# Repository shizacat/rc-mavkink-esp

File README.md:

# Description

This is hardware adapter for ESP8266 (ESP12E). The project made in Eagle.

Feature:

- Tolerant to 3.3 - 5V power supply

Firmware: [dogmaphobic/mavesp8266](https://github.com/dogmaphobic/mavesp8266)

Example:

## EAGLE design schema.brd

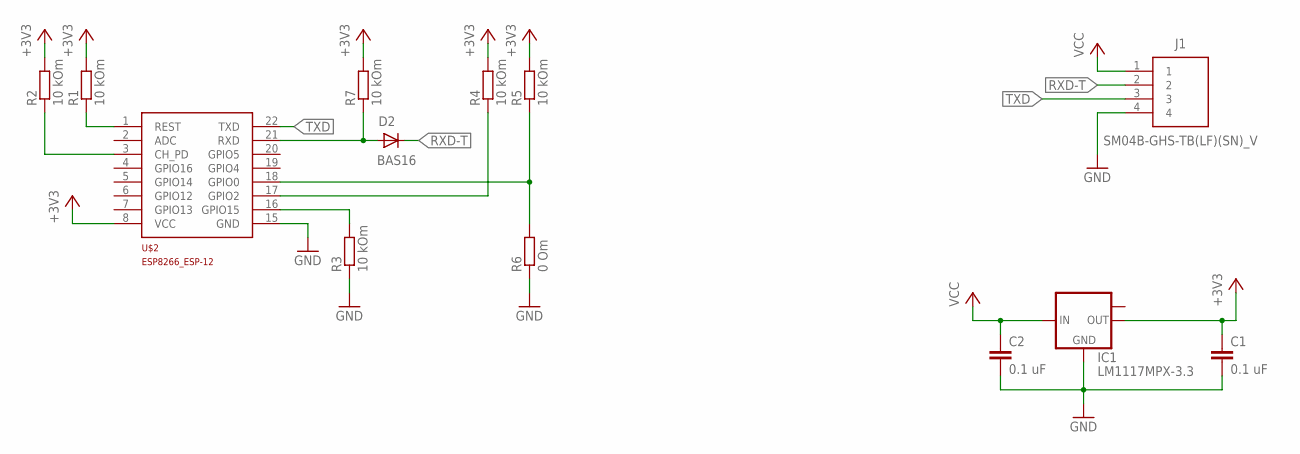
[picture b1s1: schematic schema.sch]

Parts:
C1, C2: 0.1 uF; C0603
D2: BAS16; SOT23
IC1: LM1117MPX-3.3; SOT223
J1: SM04B-GHS-TB(LF)(SN)_V; SM04B-GHS-TB
R1, R2, R3, R4, R5, R7: 10 kOm; R0603
R6: 0 Om; R0603
U$2: ESP8266_ESP-12F; ESP8266-ESP12

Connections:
+3V3: C1.1, IC1.2 (OUT), R1.2, R2.2, R4.2, R5.2, R7.2, U$2.8 (VCC)
GND: C1.2, C2.2, IC1.1 (GND), J1.4, R3.1, R6.1, U$2.15 (GND)
unnamed: R1.1, U$2.1 (REST)
unnamed: R2.1, U$2.3 (CH_PD)
unnamed: R3.2, U$2.16 (GPIO15)
unnamed: R4.1, U$2.17 (GPIO2)
unnamed: R5.1, R6.2, U$2.18 (GPIO0)
RXD: D2.1 (A), R7.1, U$2.21 (RXD)
RXD-T: D2.3 (K), J1.2
TXD: J1.3, U$2.22 (TXD)
VCC: C2.1, IC1.3 (IN), J1.1

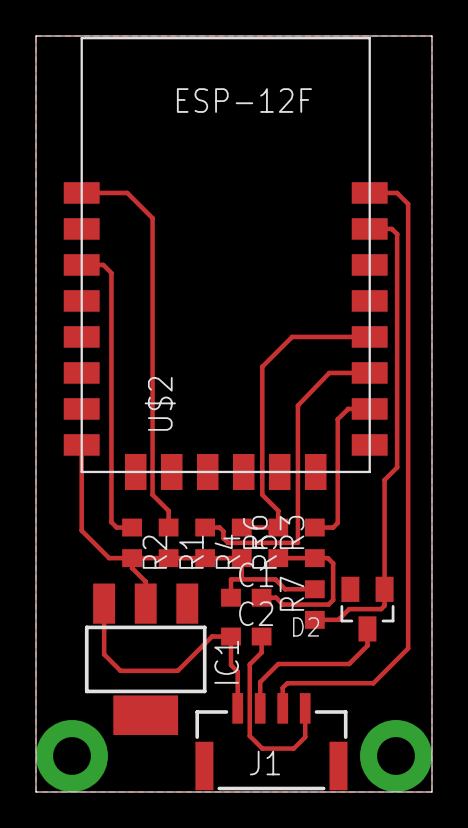
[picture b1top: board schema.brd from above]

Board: 2 copper layers, 22.0 x 42.0 mm, 13 parts (0 on the bottom side), 11 nets.

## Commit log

2020-10-05 Start
